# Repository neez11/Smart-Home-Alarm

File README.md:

# Smart Home Alarm

A local smart home alarm built with Raspberry Pi Zero WH, featuring PIR motion detection, LED and buzzer alarm feedback, Zigbee/MQTT door monitoring, camera support, a web dashboard and custom PCB design.

---

# Development
This project was developed as a group project in Electrical Engineering.

Contributors:
- [@neez11](https://github.com/neez11)
- [@abbefakih](https://github.com/abbefakih)
- [@MarcusAtaseven](https://github.com/MarcusAtaseven)
- [@Samy-Jomma](https://github.com/Samy-Jomma)

---

## Overview

This project is a smart home alarm prototype designed to run **locally without cloud services**.  
It combines embedded hardware, wireless communication, backend logic, a web-based dashboard, PCB design, and a 3D-printed enclosure into one complete system.

The system is built around a **Raspberry Pi Zero WH** and can:

- detect motion using a PIR sensor
- detect door/window events using a Zigbee sensor
- trigger local alarm feedback using LED and buzzer
- log events in the backend
- show live status in a web dashboard
- display a camera feed during alarm events
- run locally without relying on external cloud platforms

---

## Final Product

### Final assembled product

---

## Hardware Components

- Raspberry Pi Zero WH
- PIR sensor
- LED
- buzzer
- 220 Ω resistors
- SONOFF SNZB-04P Zigbee door/window sensor
- Zigbee USB adapter
- micro-USB OTG adapter
- Raspberry Pi camera module
- custom PCB
- 3D-printed enclosure

---

## System Architecture

The project is divided into the following parts:

### Local Hardware
- PIR sensor
- LED
- buzzer
- Raspberry Pi GPIO connections
- custom PCB

### Wireless Sensor Layer
- Zigbee door/window sensor
- Zigbee USB gateway
- Zigbee2MQTT
- MQTT messaging

### Software
- Python backend
- alarm logic
- event logging
- camera service
- REST API

### User Interface
- React/Vite frontend
- live system status
- event timeline
- control buttons
- camera view

### Deployment
- local hosting on Raspberry Pi
- Nginx as web server / reverse proxy

---

## Hardware Prototype

### Prototype wiring and components

### Raspberry Pi GPIO reference

---

## Schematic and PCB Design

The PCB was designed in **KiCad** based on the local hardware part of the system.

### KiCad schematic

### PCB layout

### Manufactured PCB

The PCB includes the local electronics for:

- Raspberry Pi header
- PIR sensor connection
- LED connection
- buzzer connection
- resistors

The camera and Zigbee door sensor are handled separately and are not mounted directly on the PCB.

---

## 3D Enclosure Design

A custom enclosure was designed to make the prototype more compact and easier to demonstrate.

### Enclosure lid CAD

### Main enclosure CAD

---

## How the System Works

1. The Raspberry Pi continuously monitors the PIR sensor and listens for door sensor events.
2. If motion is detected or the door opens while the system is armed:
   - the alarm state is triggered
   - LED and buzzer are activated
   - the event is logged
   - the web dashboard updates automatically
   - the camera can be used for visual verification
3. The user can monitor and control the system through the local web interface.

---

## Network Communication

The door/window sensor is not connected directly to the GPIO pins.  
Instead, it communicates wirelessly over **Zigbee**.

The communication flow is:

`Door Sensor -> Zigbee -> Zigbee USB Adapter -> Zigbee2MQTT -> MQTT -> Python Backend -> Frontend`

The PIR sensor, LED, and buzzer are connected locally to the Raspberry Pi.

---

## Web Dashboard

The web interface is used to monitor and control the system in real time.

It shows:

- alarm status
- motion status
- door status
- LED status
- buzzer status
- camera status
- event log
- control buttons for arm / disarm / reset / test

### Login page

### Dashboard overview

### Control panel and standby camera area

### Alarm camera view

### Live event log

### Hardware status section

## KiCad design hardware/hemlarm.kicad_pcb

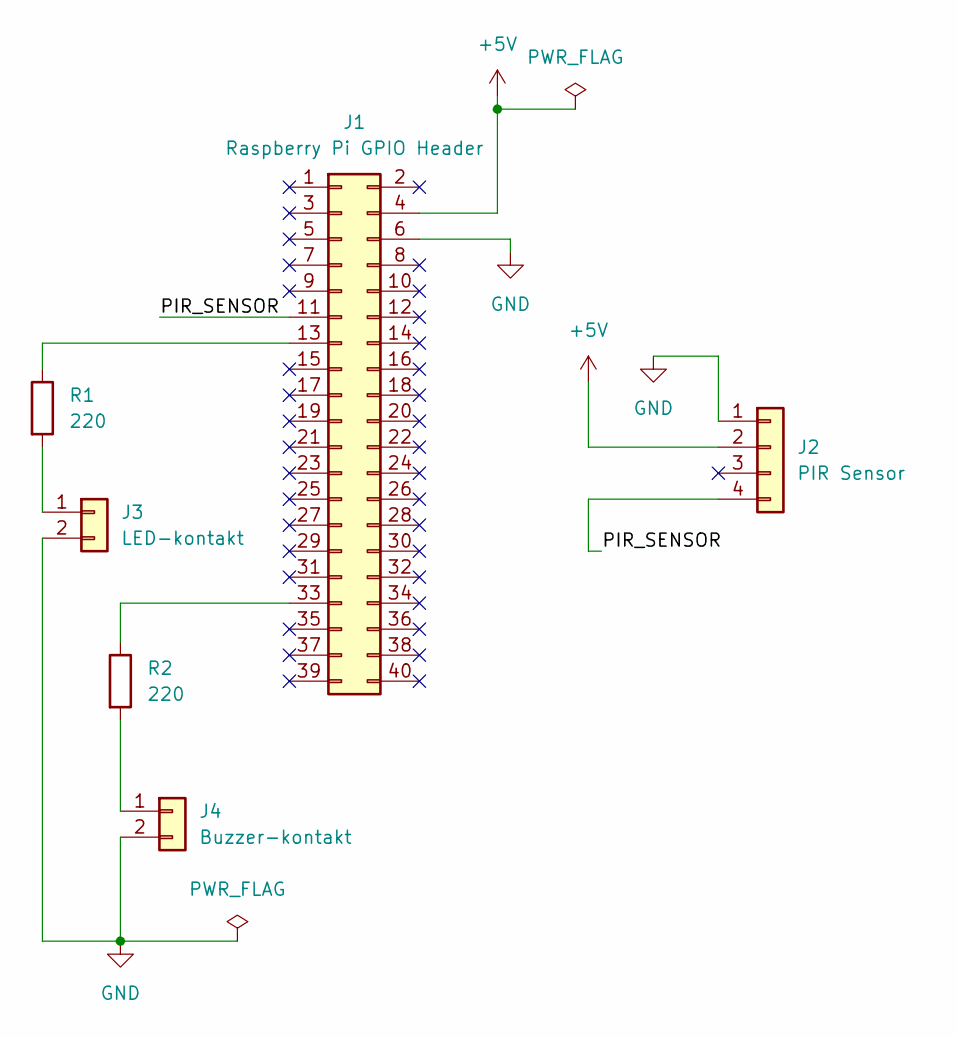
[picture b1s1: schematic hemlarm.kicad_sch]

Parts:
J1: Raspberry Pi GPIO Header; PinHeader_2x20_P2.54mm_Vertical
J2: PIR Sensor; PinHeader_1x04_P2.54mm_Vertical
J3: LED-kontakt; PinHeader_1x02_P2.54mm_Vertical
J4: Buzzer-kontakt; PinHeader_1x02_P2.54mm_Vertical
R1, R2: 220; R_Axial_DIN0207_L6.3mm_D2.5mm_P7.62mm_Horizontal

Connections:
+5V: J1.4, J2.2
/PIR_SENSOR: J1.11, J2.4
GND: J1.6, J2.1, J3.2, J4.2
unnamed: J1.13, R1.1
unnamed: J1.33, R2.1
unnamed: J3.1, R1.2
unnamed: J4.1, R2.2

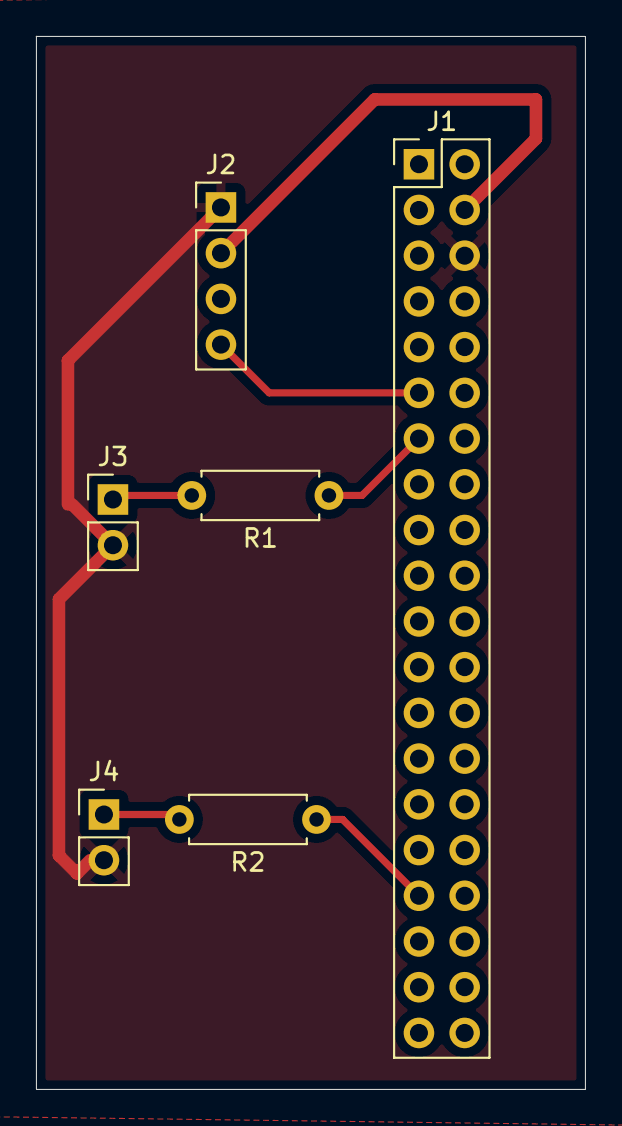
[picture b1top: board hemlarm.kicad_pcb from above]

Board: 2 copper layers, 30.5 x 58.5 mm, 6 parts (0 on the bottom side), 7 nets.

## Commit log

2026-05-26 Initial clean commit
2026-06-08 Smart Home Alarm
